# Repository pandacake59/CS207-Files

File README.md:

# CS207- Project Files
# D&Dice Roller

This project is a dice roller made specifically for Dungeons & Dragons. When playing D&D there are a large amount of different dice needed when rolling for spells, to attack, or for damage. 

This dice roller helps the user limit the amount of dice needed and helps save time when they need to roll damage for a fireball.

The project is made with an Arduino Uno, and uses a 4x4 keypad as an input while using a LCD screen and speaker as an output.

Repository Contents
===================

    ├── build                  # Compiled files 
    ├── img                    # Image files
    ├── lib                    # Library files
    ├── schematic              # Schematic files
    ├── src                    # Source files
    ├── LICENSE
    └── README.md

Requirements and Materials
===================
Libraries:
* LCD screen library for **I2C LiquidCrystal_I2C.zip**
* Keypad library **index.zip**

Materials:
* 1 x Arduino Uno R3
* 1 x Mini Metal Speaker w/ Wires - 8 ohm 0.5W
* 1 x 4x4 Keypad
* 1 x 16x2 LCD Screen
* 1 x 2.2k Resistor
* 1 x 10uF Capacitor
* 1 x KSP 2222A NPN Transistor
* 1 x Breadboard
* Wires

Build Instructions
===================
This will be the build guide in order to recreate the D&Dice Roller.

The schematic shown below will help identify the wires and the connections needed from each input/output to the pins on the Arduino.

The breadboard diagram shown below will help give another view of the connections needed for the D&Dice Roller.

The first step would be to solder (or some otherway of connecting) eight pins which will allow the keypad to be used as an input device. And then connecting the pins onto the digital ports from numbers 2~9.

Next would be connecting the I2C of the LCD screen to the Arduino board
**GND -- GND**
**VCC -- 5V**
**SDA -- A4**
**SCL -- A5**

The last part will be creating the speaker amplification circuit and connecting it to digital pin 11.

Optionally you can include a power supply to connect directly to the Arduino Uno board to allow for more mobility

The completed build will look something like this

Usage
===================
1.	On the keypad pick the amount of dice you would like to roll between 1-99.
2.	Press the D key to input the amount of dice.
3.	Pick the sided dice you would like to roll between 1-99.
4.	(Optional) press the + or – key on the keypad if you would like to add any modifiers to the roll.
5.	Press the enter key to roll your dice.
6.	Press the C key afterwards or during any time when inputting the values.
7.	Press the backspace key if any mistakes were made.

*

Credits
===================
Michael Smith - Speaker output for Arduino

Junez Riyaz - Audio Amplifier using transistor

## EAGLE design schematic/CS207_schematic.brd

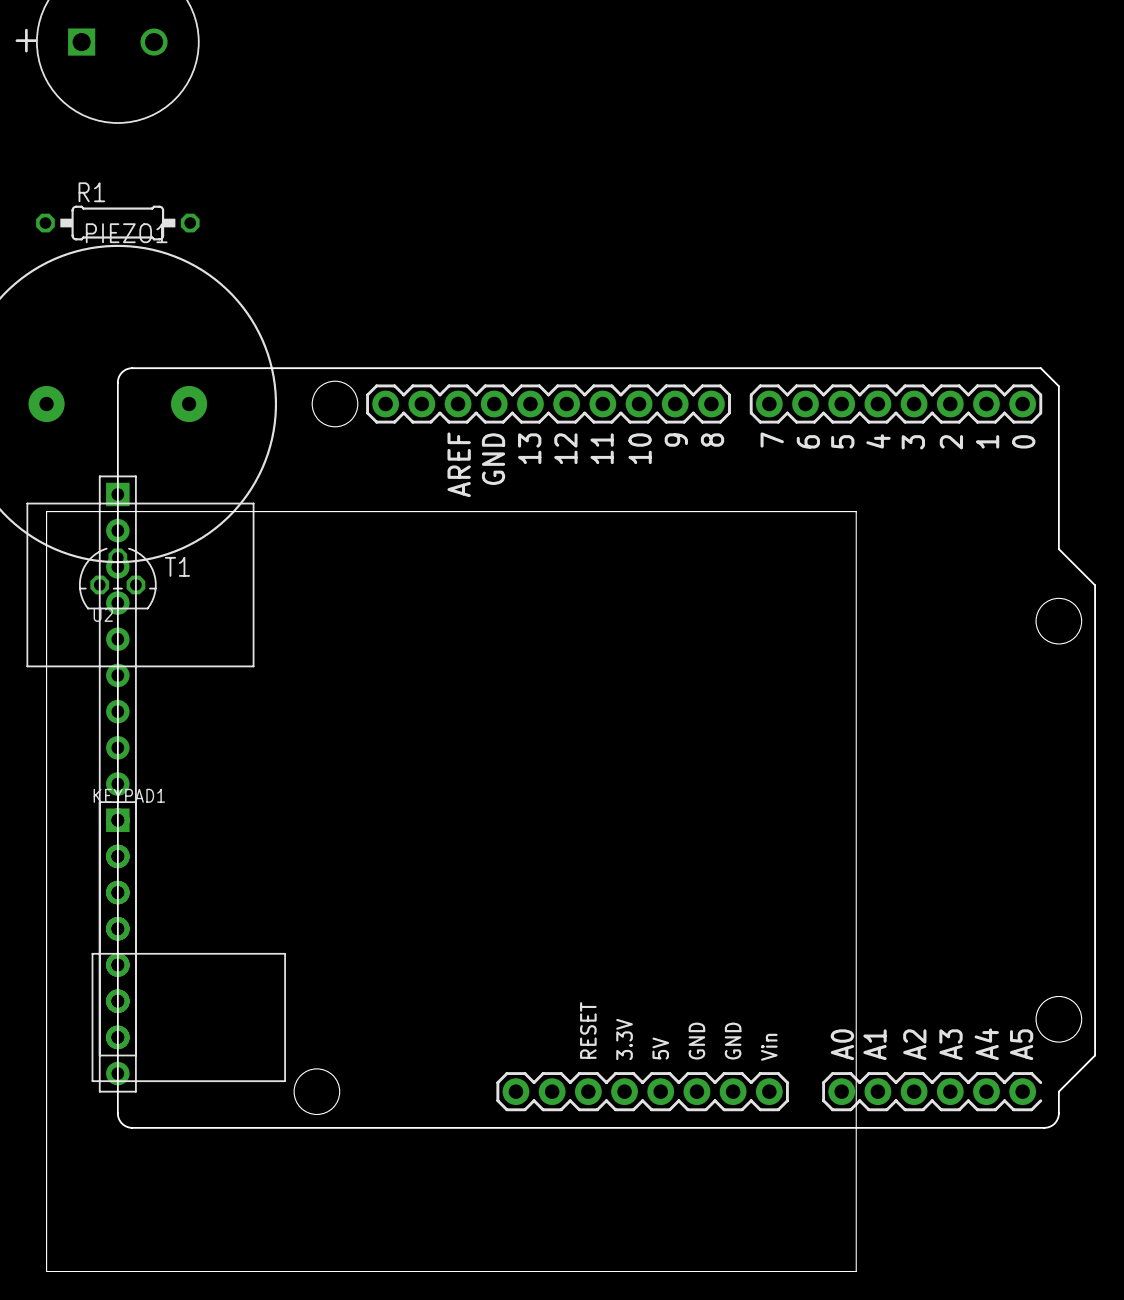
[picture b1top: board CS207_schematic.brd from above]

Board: 2 copper layers, 73.6 x 63.4 mm, 7 parts (0 on the bottom side), 16 nets, no tracks yet.

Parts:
C1: 10uF; RADIAL-D11.36MM
KEYPAD1: 1X8P-2.54-2.54-11.6-3.0-BLACK-MALE
PIEZO1: PIEZO-22MM
R1: 2.2k‎Ω; 0207/10
T1: TO92
U1: ARDUINO_UNO
U2: 1X16P-2.54-2.54-11.6-3.0-BLACK-MALE

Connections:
unnamed: KEYPAD1.1, U1.2
unnamed: KEYPAD1.2, U1.3
unnamed: KEYPAD1.3, U1.4
unnamed: KEYPAD1.4, U1.5
unnamed: KEYPAD1.5, U1.6
unnamed: KEYPAD1.6, U1.7
unnamed: KEYPAD1.7, U1.8
unnamed: KEYPAD1.8, U1.9
unnamed: R1.1, T1.2
unnamed: T1.1, U1.GND..
unnamed: C1.-, U1.11
unnamed: C1.+, PIEZO1.P$2, R1.2, T1.3
unnamed: PIEZO1.P$1, U1.5V, U2.2
unnamed: U1.GND., U2.1
unnamed: U1.A5, U2.4
unnamed: U1.A4, U2.5
